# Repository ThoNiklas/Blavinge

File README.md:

# Blåvinge 
This keyboard is my variation of the keyboard ['Absolem' by MrZealot](https://github.com/mrzealot/absolem).<br>
The main differences are adjusted key positions and a changed key layout.

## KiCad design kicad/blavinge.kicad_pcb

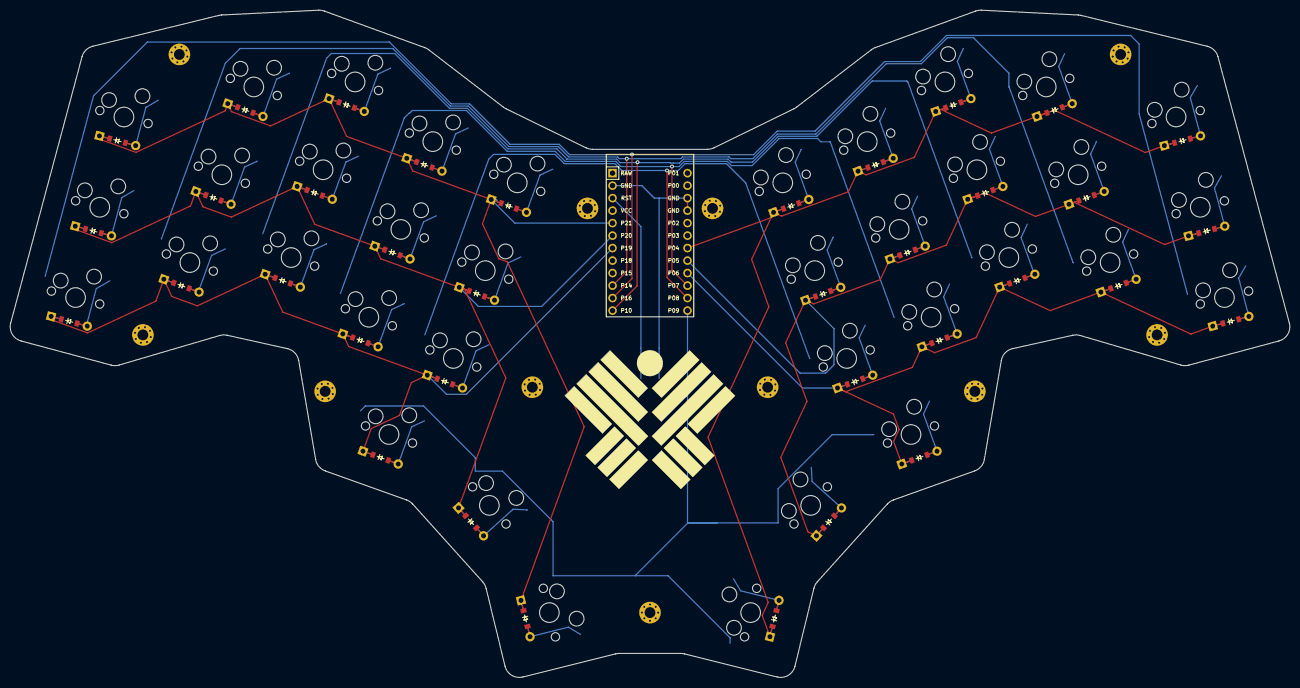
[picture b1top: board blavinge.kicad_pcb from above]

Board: 2 copper layers, 260.2 x 135.7 mm, 85 parts (1 on the bottom side), 50 nets.

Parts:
B1: SW_TACT_ALPS_SKQGABE010
D1, D2, D3, D4, D5, D6, D7, D8, D9, D10, D11, D12, D13, D14, D15, D16, D17, D18, D19, D20, D21, D22, D23, D24, D25, D26, D27, D28, D29, D30, D31, D32, D33, D34, D35, D36: ComboDiode
MCU1: ProMicro
S1, S2, S3, S4, S5, S6, S7, S8, S9, S10, S11, S12, S13, S14, S15, S16, S17, S18, S19, S20, S21, S22, S23, S24, S25, S26, S27, S28, S29, S30, S31, S32, S33, S34, S35, S36: MX
_1, _2, _3, _4, _5, _6, _7, _8, _9, _10, _11: MountingHole_2.2mm_M2_Pad_Via

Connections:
GND: B1.1, MCU1.2, MCU1.15, MCU1.16
P4: D21.1, D24.1, D27.1, D30.1, D33.1, D36.1, MCU1.19
P5: D20.1, D23.1, D26.1, D29.1, D32.1, D35.1, MCU1.20
P6: D19.1, D22.1, D25.1, D28.1, D31.1, D34.1, MCU1.21
P7: MCU1.22, S10.1, S11.1, S12.1, S28.1, S29.1, S30.1
P8: MCU1.23, S13.1, S14.1, S15.1, S31.1, S32.1, S33.1
P9: MCU1.24, S16.1, S17.1, S18.1, S34.1, S35.1, S36.1
P10: MCU1.12, S7.1, S8.1, S9.1, S25.1, S26.1, S27.1
P14: MCU1.10, S4.1, S5.1, S6.1, S22.1, S23.1, S24.1
P16: MCU1.11, S1.1, S2.1, S3.1, S19.1, S20.1, S21.1
P19: D1.1, D4.1, D7.1, D10.1, D13.1, D16.1, MCU1.7
P20: D2.1, D5.1, D8.1, D11.1, D14.1, D17.1, MCU1.6
P21: D3.1, D6.1, D9.1, D12.1, D15.1, D18.1, MCU1.5
RST: B1.2, MCU1.3
far_thumb: D18.2, S18.2
home_thumb: D17.2, S17.2
index_bottom: D10.2, S10.2
index_home: D11.2, S11.2
index_top: D12.2, S12.2
inner_bottom: D13.2, S13.2
inner_home: D14.2, S14.2
inner_top: D15.2, S15.2
middle_bottom: D7.2, S7.2
middle_home: D8.2, S8.2
middle_top: D9.2, S9.2
mirror_far_thumb: D36.2, S36.2
mirror_home_thumb: D35.2, S35.2
mirror_index_bottom: D28.2, S28.2
mirror_index_home: D29.2, S29.2
mirror_index_top: D30.2, S30.2
mirror_inner_bottom: D31.2, S31.2
mirror_inner_home: D32.2, S32.2
mirror_inner_top: D33.2, S33.2
mirror_middle_bottom: D25.2, S25.2
mirror_middle_home: D26.2, S26.2
mirror_middle_top: D27.2, S27.2
mirror_near_thumb: D34.2, S34.2
mirror_pinky_bottom: D19.2, S19.2
mirror_pinky_home: D20.2, S20.2
mirror_pinky_top: D21.2, S21.2
mirror_ring_bottom: D22.2, S22.2
mirror_ring_home: D23.2, S23.2
mirror_ring_top: D24.2, S24.2
near_thumb: D16.2, S16.2
pinky_bottom: D1.2, S1.2
pinky_home: D2.2, S2.2
pinky_top: D3.2, S3.2
ring_bottom: D4.2, S4.2
ring_home: D5.2, S5.2
ring_top: D6.2, S6.2

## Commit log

2024-09-26 updated .gitignore
2024-09-26 Added footprint of mounting hole
2024-09-28 deleted cases
2024-09-29 Added cost calculation and did new PCB with mounting holes
2024-09-29 Added interactive key layout
2024-09-29 Updated .gitigonre to ignore generated kicasd files
2024-09-29 Deleted gerber files
2024-09-29 Deleted kicad project files
2024-09-29 Replaced PCB with one with more mounting holes, no routing
2024-09-29 .step of PCB added
2024-09-29 Sketch of the middle part of the case
2024-09-30 Added first sketch of the logo
2024-09-30 Updated .gitignore, final logo
2024-09-30 Changed color for the logo
2024-09-30 Complete case with mounting holes finished
2024-10-01 Added QMK
2024-10-01 changed key layout
2024-10-01 Added backup of the keyboard
2024-10-02 Final routing
2024-10-02 Final PCB
2024-10-02 Added logo.png for README.me
2024-10-02 Changed logo size
2024-10-03 Added gerber file for jlcpcb
2024-10-03 Added logo to silkscreen
2024-10-03 Added stuff to the silkscreen, added grid
2024-10-23 Fixed layout
2024-10-23 Added qmk_firmware as submodule
2024-10-23 changed .gitignore
2024-10-27 Little changes overall
2024-10-28 Added a 1 part case
2024-11-16 Added other case variant
2024-11-17 Changed layout
2024-11-22 First version of BT case
2024-11-28 Fixed bottom part of the case and the layout
2024-12-17 Changed layout to qwerty
2025-02-24 Key layout sketch changed
2025-02-24 Added *.bak to .gitignore
